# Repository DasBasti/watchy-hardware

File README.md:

# Schmartwatch 2.0 (fork watchy-hardware)
Modified Watchy Hardware CAD Files

Changes to original Watchy:
* DCDC switch mode power supply
* RV-3028-C7 RTC
* supporting 3-color e-Paper display

Read the docs at [https://watchy.sqfmi.com/](https://watchy.sqfmi.com/)
More information at [http://schmartwatch.com](http://schmartwatch.com/)

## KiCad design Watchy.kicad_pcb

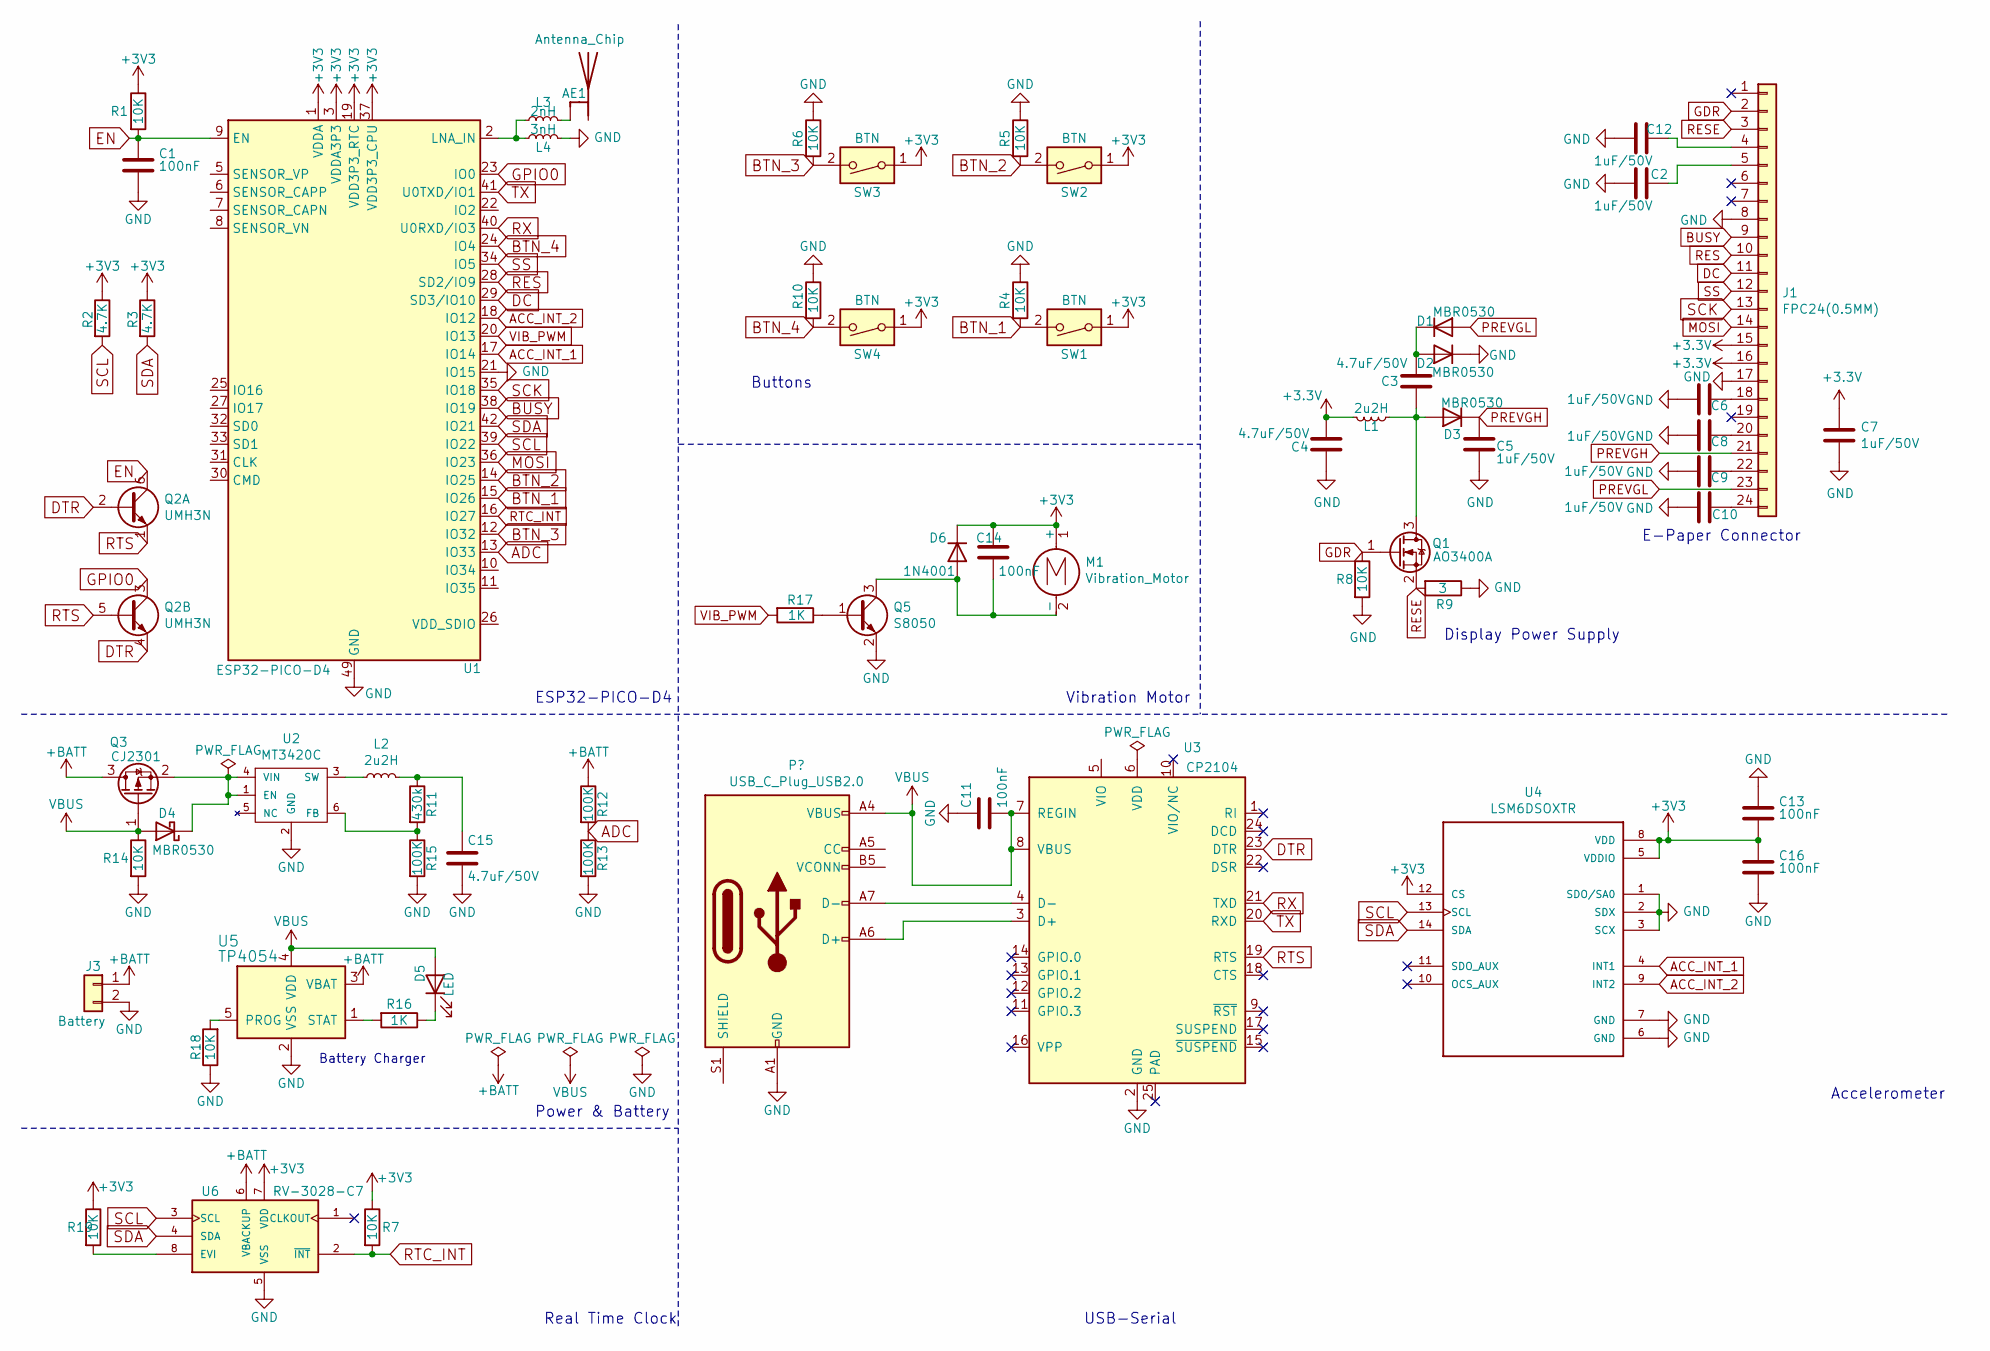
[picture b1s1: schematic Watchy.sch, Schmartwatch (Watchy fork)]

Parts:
AE1: Antenna_Chip; ANT_ANT016008LCS2442MA2
C1, C11, C13, C14, C16: 100nF; C_0603_1608Metric
C2, C5, C6, C7, C8, C9, C10, C12: 1uF/50V; C_0603_1608Metric
C3, C4, C15: 4.7uF/50V; C_0805_2012Metric
D1, D2, D3, D4: MBR0530; D_SOD-123
D5: LED; LED_0603_1608Metric
D6: 1N4001; D_SOD-123F
J1: FPC24(0.5MM); 24_Pins_0.5mm_Pitch_ZIF_Connector_UP
J3: Battery; 1.25T-2PWT (Molex 532610271)
L1, L2: 2u2H; L_0603_1608Metric; MPN KPS0603LD2R2KST
L3: 2nH; L_0402_1005Metric; MPN SWPA252012S2R2MT
L4: 3nH; L_0402_1005Metric; MPN SWPA252012S2R2MT
M1: Vibration_Motor; Motor_Header; MPN C1026B002F
Q1: AO3400A; SOT-23
Q2: UMH3N; SOT-363_SC-70-6
Q3: CJ2301; SOT-23
Q5: S8050; SOT-23
R1, R4, R5, R6, R7, R8, R10, R14, R18, R19: 10K; R_0402_1005Metric
R2, R3: 4.7K; R_0402_1005Metric
R9: 3; R_0402_1005Metric
R11: 430k; R_0402_1005Metric; MPN 0402WGF4303TCE
R12, R13, R15: 100K; R_0402_1005Metric
R16, R17: 1K; R_0402_1005Metric
SW1, SW2, SW3, SW4: BTN; K2-1114SA-A4SW-06
U1: ESP32-PICO-D4; QFN-48-1EP_7x7mm_P0.5mm_EP5.45x5.45mm
U2: MT3420C; SOT-23-6; MPN MT3420C; LCSC_PN C181741
U3: CP2104; QFN-24-1EP_4x4mm_Pitch0.5mm
U4: LSM6DSOXTR; PQFN50P250X300X86-14N
U5: TP4054; SOT-23-5
U6: RV-3028-C7; IC_RV-3028-C7; PARTREV 1.1

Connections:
+BATT: J3.1, Q3.3 (D), R12.1, U5.3 (VBAT), U6.6 (VBACKUP)
ACC_INT_1: U1.17 (IO14), U4.4 (INT1)
ACC_INT_2: U1.18 (IO12), U4.9 (INT2)
ADC: R12.2, R13.1, U1.13 (IO33)
BTN_1: R4.2, SW1.2, U1.15 (IO26)
BTN_2: R5.2, SW2.2, U1.14 (IO25)
BTN_3: R6.2, SW3.2, U1.12 (IO32)
BTN_4: R10.2, SW4.2, U1.24 (IO4)
BUSY: J1.9, U1.38 (IO19)
DC: J1.11, U1.29 (SD3/IO10)
DTR: Q2.2 (B1), Q2.4 (E2), U3.23 (DTR)
EN: C1.1, Q2.6 (C1), R1.2, U1.9 (EN)
GDR: J1.2, Q1.1 (G), R8.1
GND: C1.2, C2.2, C4.2, C5.2, C6.2, C7.2, C8.2, C9.2, C10.2, C11.1, C12.2, C13.1, C15.2, C16.2, D2.1 (K), J1.8, J1.17, J3.2, L4.2, Q5.2 (E), R4.1, R5.1, R6.1, R8.2, R9.1, R10.1, R13.2, R14.2, R15.2, R18.1, U1.21 (IO15), U1.49 (GND), U2.2 (GND), U3.2 (GND), U4.1 (SDO/SA0), U4.2 (SDX), U4.3 (SCX), U4.6 (GND), U4.7 (GND), U5.2 (VSS), U6.5 (VSS)
GPIO0: Q2.3 (C2), U1.23 (IO0)
MOSI: J1.14, U1.36 (IO23)
unnamed: AE1.4 (FEED), L3.2
unnamed: C2.1, J1.5
unnamed: C3.1, D1.1 (K), D2.2 (A)
unnamed: C3.2, D3.2 (A), L1.1, Q1.3 (D)
unnamed: C6.1, J1.18
unnamed: C8.1, J1.20
unnamed: C9.1, J1.22
unnamed: C10.1, J1.24
unnamed: C12.1, J1.4
unnamed: C14.2, D6.2 (A), M1.2 (-), Q5.3 (C)
unnamed: C15.1, L2.2, R11.1
unnamed: D4.1 (K), Q3.2 (S), U2.1 (EN), U2.4 (VIN)
unnamed: D5.1 (K), R16.1
unnamed: L2.1, U2.3 (SW)
unnamed: L3.1, L4.1, U1.2 (LNA_IN)
unnamed: Q5.1 (B), R17.1
unnamed: R11.2, R15.1, U2.6 (FB)
unnamed: R16.2, U5.1 (STAT)
unnamed: R18.2, U5.5 (PROG)
unnamed: R19.2, U6.8 (EVI)
PREVGH: C5.1, D3.1 (K), J1.21
PREVGL: D1.2 (A), J1.23
RES: J1.10, U1.28 (SD2/IO9)
RESE: J1.3, Q1.2 (S), R9.2
RTC_INT: R7.2, U1.16 (IO27), U6.2 (~INT)
RTS: Q2.1 (E1), Q2.5 (B2), U3.19 (RTS)
RX: U1.40 (U0RXD/IO3), U3.21 (TXD)
SCK: J1.13, U1.35 (IO18)
SCL: R2.2, U1.39 (IO22), U4.13 (SCL), U6.3 (SCL)
SDA: R3.2, U1.42 (IO21), U4.14 (SDA), U6.4 (SDA)
SS: J1.12, U1.34 (IO5)
TX: U1.41 (U0TXD/IO1), U3.20 (RXD)
VBUS: C11.2, D4.2 (A), D5.2 (A), Q3.1 (G), R14.1, U3.7 (REGIN), U3.8 (VBUS), U5.4 (VDD)
VIB_PWM: R17.2, U1.20 (IO13)

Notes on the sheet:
ESP32-PICO-D4
Power & Battery
Real Time Clock
USB-Serial
Accelerometer
E-Paper Connector
Buttons
Vibration Motor
Battery Charger
Display Power Supply

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
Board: 2 copper layers, 63 parts (0 on the bottom side), 51 nets, no tracks yet.

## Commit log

2021-01-19 Modifications done during livestream 18th January 2021 for a schmartwatch 2.0 based on the Watchy
    - Use DCDC switch mode power supply
    - Change RTC to RV-3028
    - Use a chip antenna for BLE/WiFi connection
    - Review of e-Paper connector for 3 color e-ink
    - Forward annotation and initial placing done for PCB
2021-01-19 Update README.md
    Information updated for Schmartwatch fork
